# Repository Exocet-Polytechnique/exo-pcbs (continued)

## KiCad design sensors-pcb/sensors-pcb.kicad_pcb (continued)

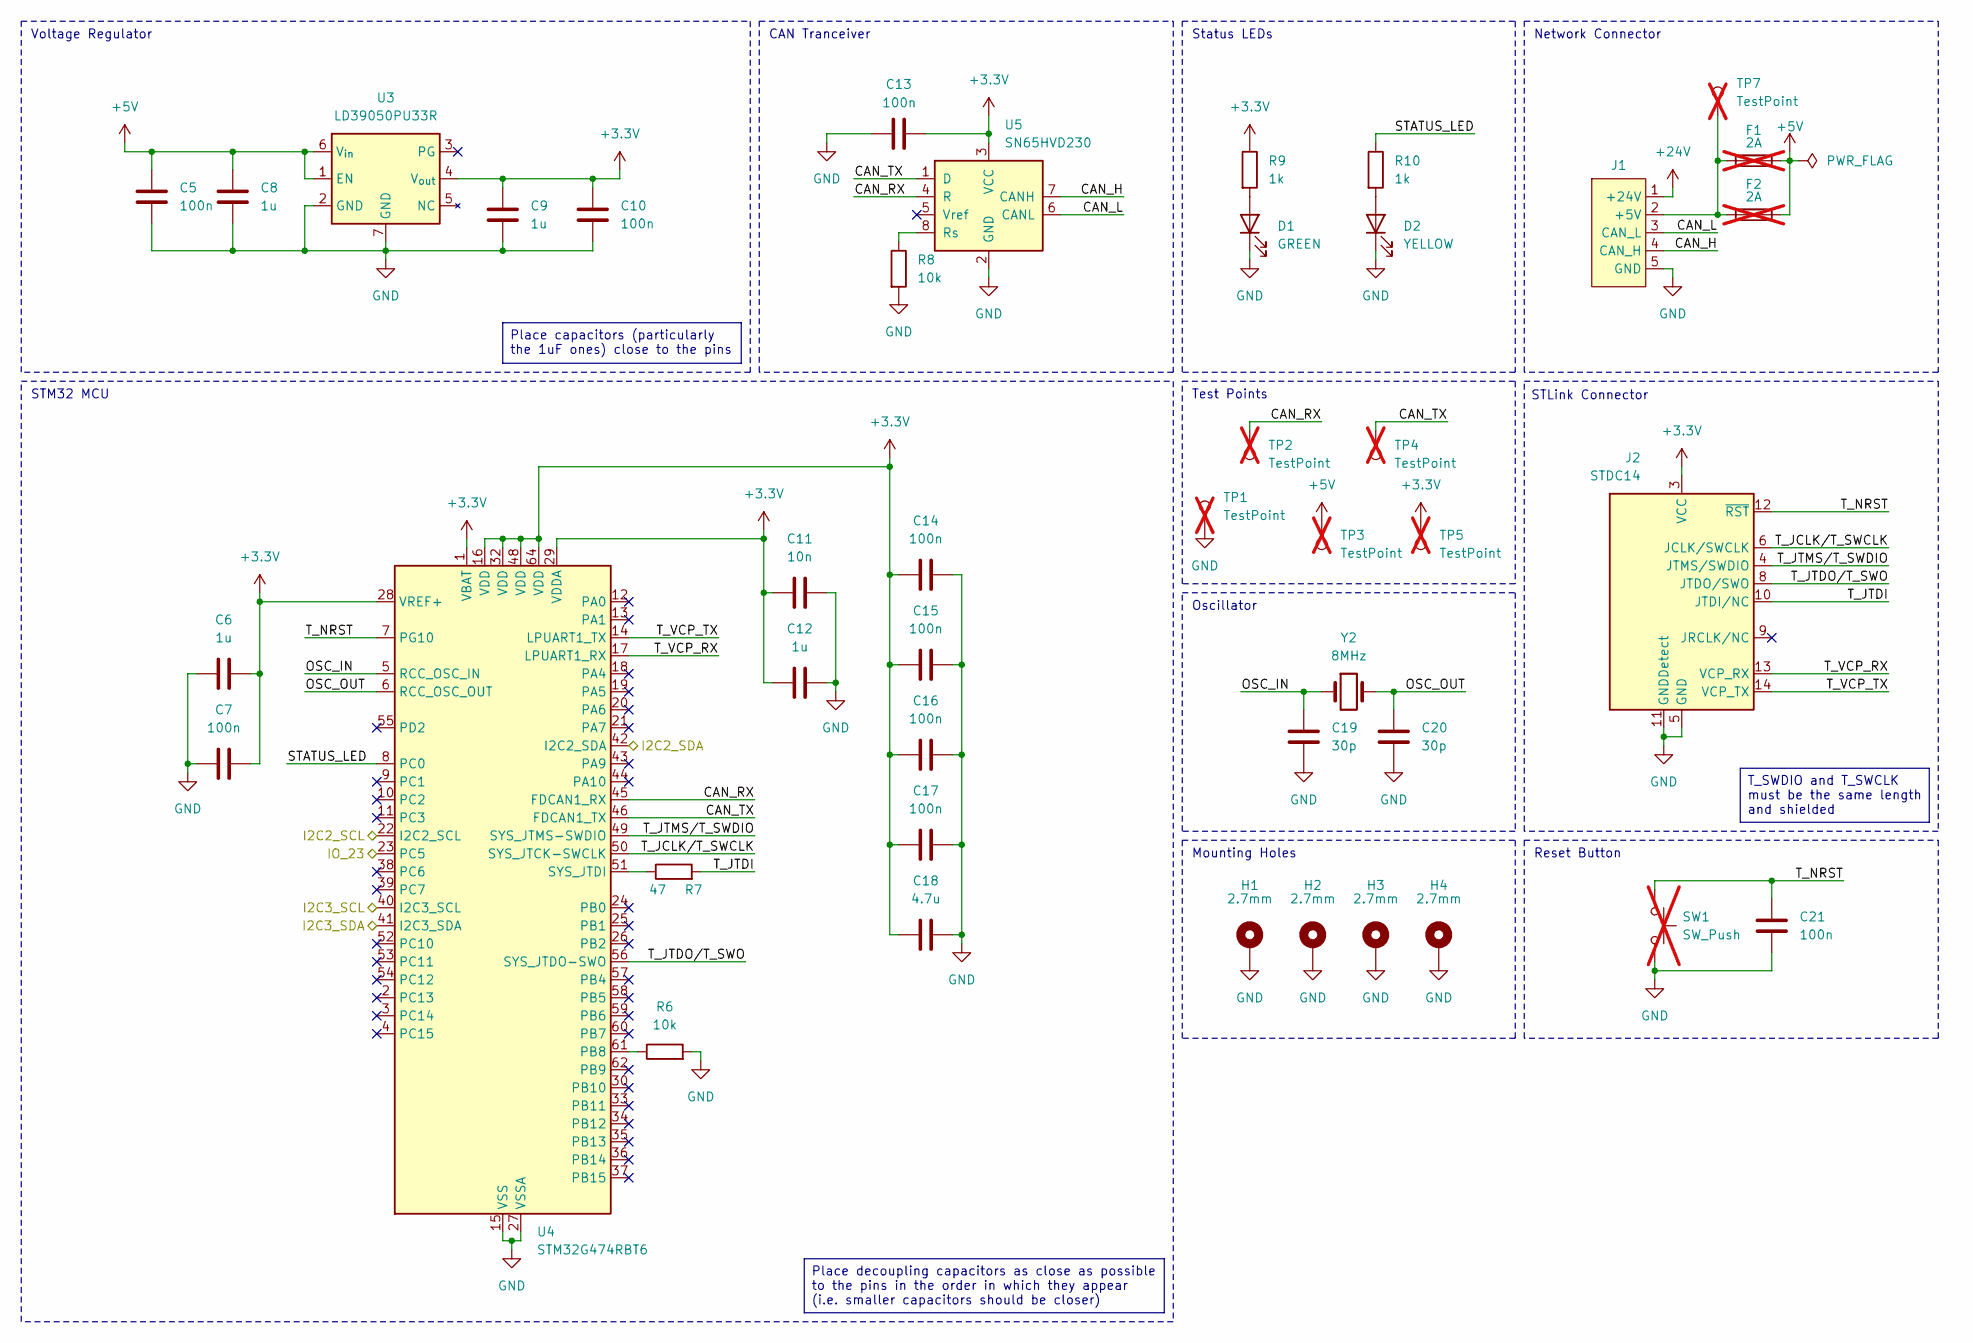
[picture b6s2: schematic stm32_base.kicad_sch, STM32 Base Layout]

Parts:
C5, C7, C10, C13, C14, C15, C16, C17, C21: 100n; C_0402_1005Metric; JLCPCB C1525
C6, C8, C9, C12: 1u; C_0402_1005Metric; JLCPCB C52923
C11: 10n; C_0402_1005Metric; JLCPCB C15195
C18: 4.7u; C_0402_1005Metric; JLCPCB C23733
C19, C20: 30p; C_0603_1608Metric; JLCPCB C1658
D1: GREEN; LED_0805_2012Metric_With_Annotations; JLCPCB C2297
D2: YELLOW; LED_0805_2012Metric_With_Annotations; JLCPCB C2296
F1: 2A; Fuse_Holder_Littelfuse_01530008; JLCPCB C206907; not fitted
F2: 2A; Fuseholder_Clip-5x20mm_Littelfuse_111_Lateral_P18.80x5.00mm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; not fitted
H1, H2, H3, H4: 2.7mm; MountingHole_2.7mm_Pad
J1: Network Connector; Molex_SPOX_5268-05A_1x05_P2.50mm_Horizontal; JLCPCB C185201
J2: STDC14; PinHeader_2x07_P1.27mm_Vertical_SMD; JLCPCB C7465995
R6, R8: 10k; R_0402_1005Metric; JLCPCB C25744
R7: 47; R_0603_1608Metric; JLCPCB C23182
R9, R10: 1k; R_0402_1005Metric; JLCPCB C11702
SW1: SW_Push; SW_PUSH_6mm; not fitted
TP1, TP2, TP3, TP4, TP5, TP7: TestPoint; TestPoint_Keystone_5005-5009_Compact; not fitted
U3: LD39050PU33R; DFN-6-1EP_3x3mm_P0.95mm_EP1.7x2.6mm; JLCPCB C132827
U4: STM32G474RBT6; LQFP-64_10x10mm_P0.5mm; JLCPCB C529413
U5: SN65HVD230; SOIC-8_3.9x4.9mm_P1.27mm; JLCPCB C12084
Y2: 8MHz; Crystal_SMD_HC49-SD; Part Name X49SM8MSD2SC; JLCPCB C12674

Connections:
+3.3V: C6.2, C7.2, C9.1, C10.1, C11.1, C12.1, C13.1, C14.1, C15.1, C16.1, C17.1, C18.1, J2.3 (VCC), R9.1, TP5.1, U3.4 (V_{out}), U4.1 (VBAT), U4.16 (VDD), U4.28 (VREF+), U4.29 (VDDA), U4.32 (VDD), U4.48 (VDD), U4.64 (VDD), U5.3 (VCC); also elsewhere on the board
+5V: C5.1, C8.1, F1.2, F2.2, TP3.1, U3.1 (EN), U3.6 (V_{in})
+24V: J1.1 (+24V)
/INT_IMU: U4.23 (PC5); also elsewhere on the board
/SCL_GPS: U4.40 (I2C3_SCL); also elsewhere on the board
/SCL_IMU: U4.22 (I2C2_SCL); also elsewhere on the board
/SDA_GPS: U4.41 (I2C3_SDA); also elsewhere on the board
/SDA_IMU: U4.42 (I2C2_SDA); also elsewhere on the board
/STM32 Base Layout/CAN_H: J1.4 (CAN_H), U5.7 (CANH)
/STM32 Base Layout/CAN_L: J1.3 (CAN_L), U5.6 (CANL)
/STM32 Base Layout/CAN_RX: TP2.1, U4.45 (FDCAN1_RX), U5.4 (R)
/STM32 Base Layout/CAN_TX: TP4.1, U4.46 (FDCAN1_TX), U5.1 (D)
/STM32 Base Layout/OSC_IN: C19.1, U4.5 (RCC_OSC_IN), Y2.1
/STM32 Base Layout/OSC_OUT: C20.1, U4.6 (RCC_OSC_OUT), Y2.2
/STM32 Base Layout/STATUS_LED: R10.1, U4.8 (PC0)
/STM32 Base Layout/T_JCLK/T_SWCLK: J2.6 (JCLK/SWCLK), U4.50 (SYS_JTCK-SWCLK)
/STM32 Base Layout/T_JTDI: J2.10 (JTDI/NC), R7.2
/STM32 Base Layout/T_JTDO/T_SWO: J2.8 (JTDO/SWO), U4.56 (SYS_JTDO-SWO)
/STM32 Base Layout/T_JTMS/T_SWDIO: J2.4 (JTMS/SWDIO), U4.49 (SYS_JTMS-SWDIO)
/STM32 Base Layout/T_NRST: C21.2, J2.12 (~RST), SW1.1, U4.7 (PG10)
/STM32 Base Layout/T_VCP_RX: J2.13 (VCP_RX), U4.17 (LPUART1_RX)
/STM32 Base Layout/T_VCP_TX: J2.14 (VCP_TX), U4.14 (LPUART1_TX)
GND: C5.2, C6.1, C7.1, C8.2, C9.2, C10.2, C11.2, C12.2, C13.2, C14.2, C15.2, C16.2, C17.2, C18.2, C19.2, C20.2, C21.1, D1.1 (K), D2.1 (K), H1.1, H2.1, H3.1, H4.1, J1.5 (GND), J2.5 (GND), J2.7 (GND), J2.11 (GNDDetect), R6.2, R8.2, SW1.2, TP1.1, U3.2 (GND), U3.7 (GND), U4.15 (VSS), U4.27 (VSSA), U4.31 (VSS), U4.47 (VSS), U4.63 (VSS), U5.2 (GND); also elsewhere on the board
unnamed: D1.2 (A), R9.2
unnamed: D2.2 (A), R10.2
unnamed: F1.1, F2.1, J1.2 (+5V), TP7.1
unnamed: R7.1, U4.51 (SYS_JTDI)
unnamed: R6.1, U4.61 (PB8)
unnamed: R8.1, U5.8 (Rs)

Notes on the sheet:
Oscillator
Reset Button
Mounting Holes
Voltage Regulator
CAN Tranceiver
Status LEDs
STLink Connector
Test Points
Network Connector
STM32 MCU
T_SWDIO and T_SWCLK must be the same length and shielded
Place capacitors (particularly the 1uF ones) close to the pins
Place decoupling capacitors as close as possible to the pins in the order in which they appear (i.e. smaller capacitors should be closer)

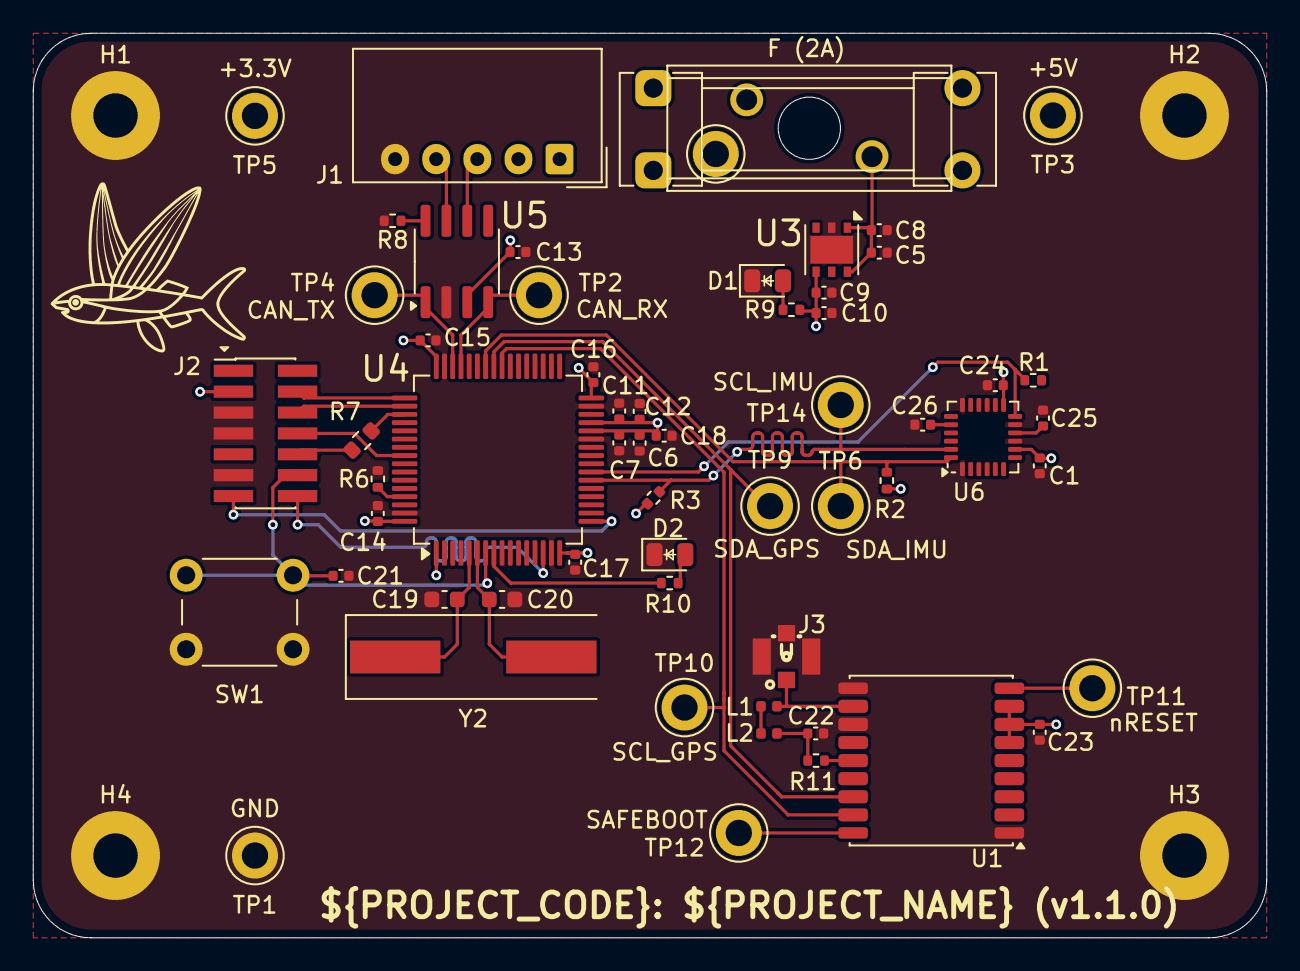
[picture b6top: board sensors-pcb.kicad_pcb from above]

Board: 2 copper layers, 75.0 x 55.0 mm, 64 parts (0 on the bottom side), 36 nets.

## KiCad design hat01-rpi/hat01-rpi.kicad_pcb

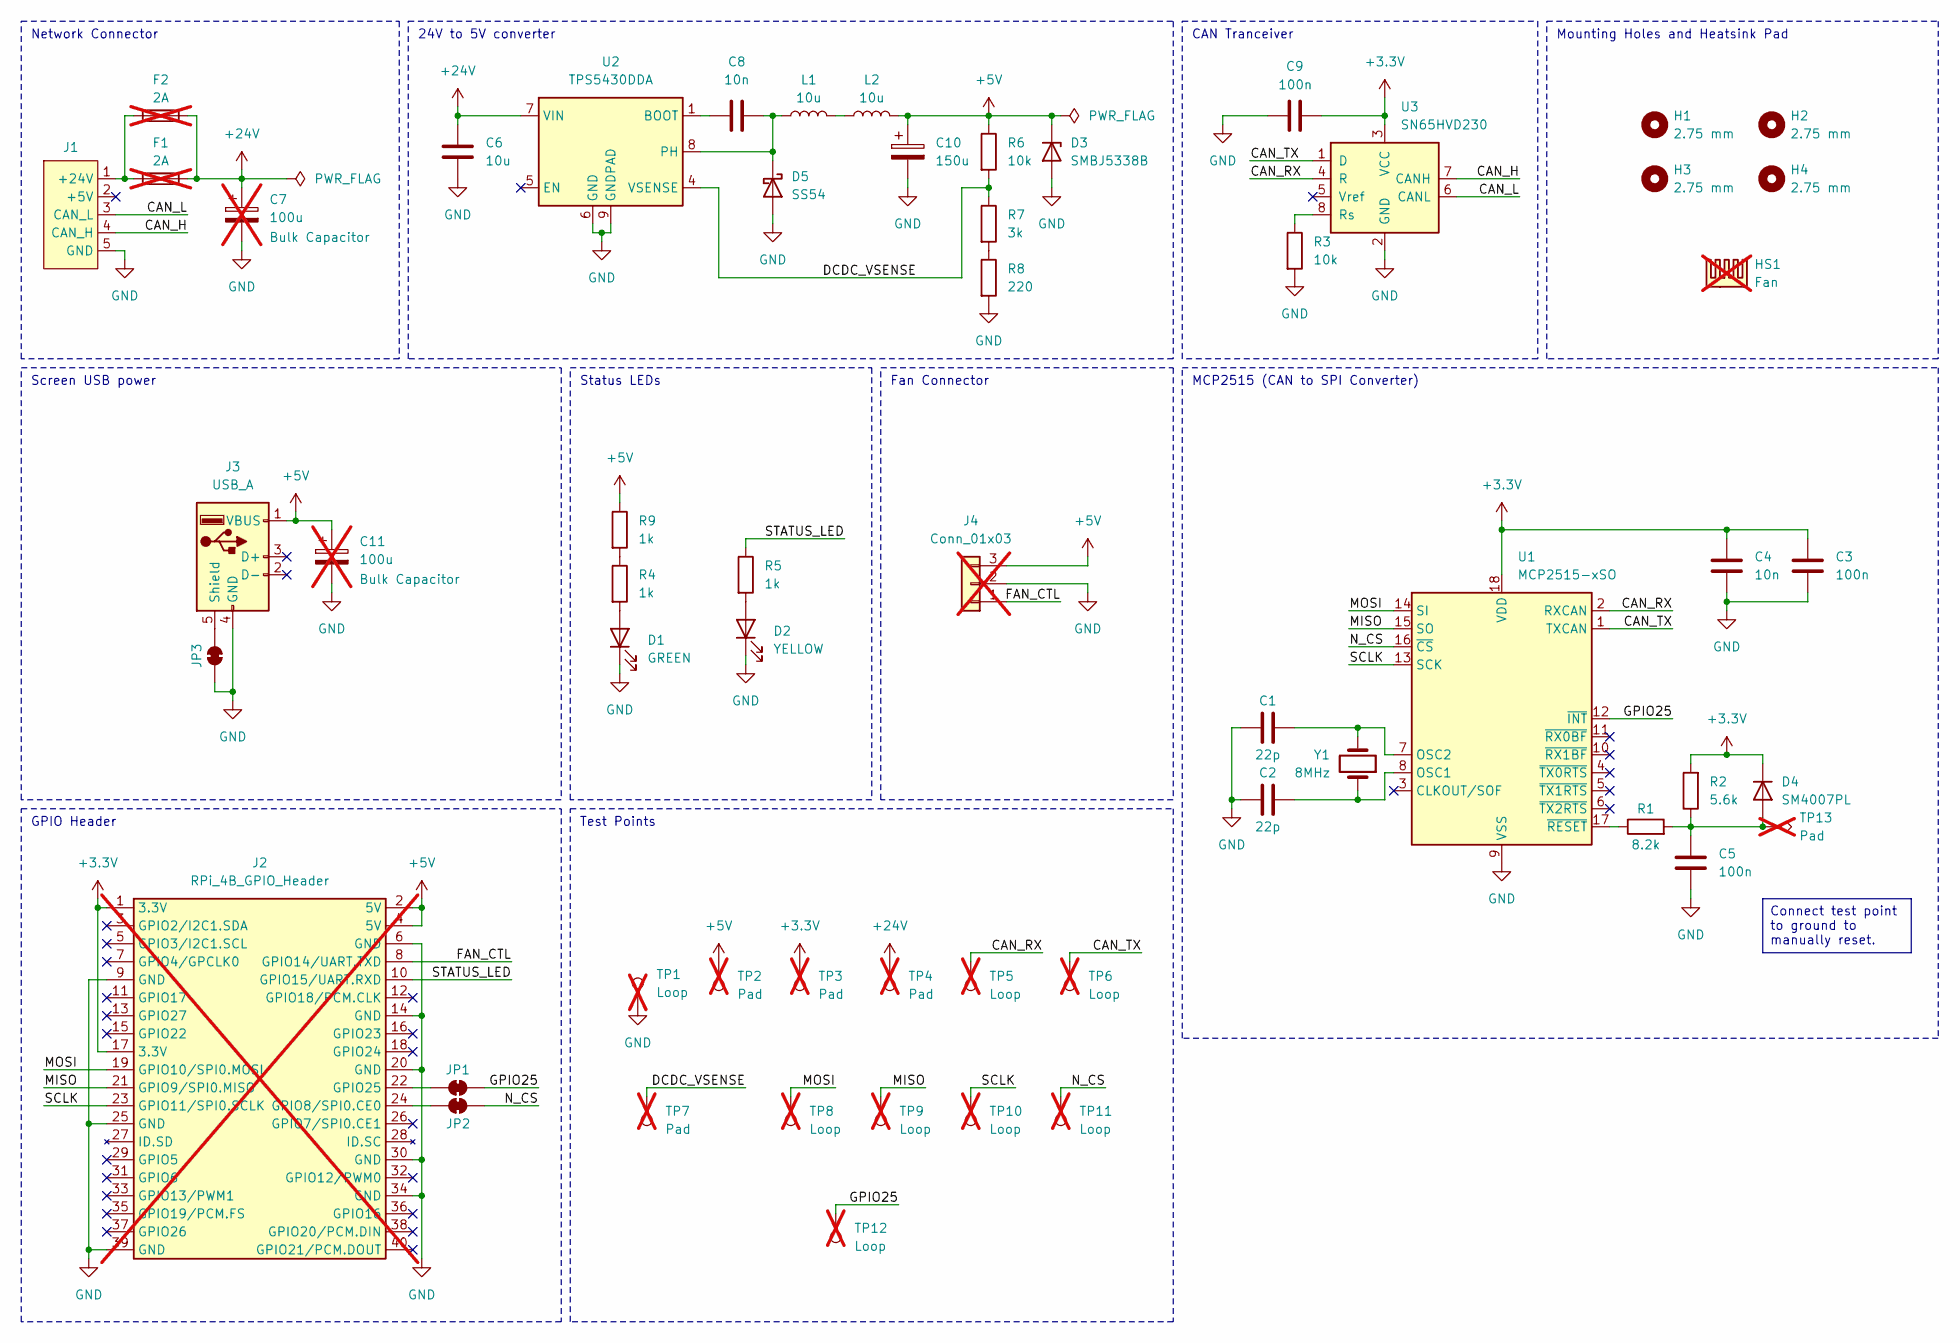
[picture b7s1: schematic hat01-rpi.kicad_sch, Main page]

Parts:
C1, C2: 22p; C_0402_1005Metric; JLCPCB C1555
C3, C5, C9: 100n; C_0402_1005Metric_Pad0.74x0.62mm_HandSolder; JLCPCB C1525
C4, C8: 10n; C_0402_1005Metric_Pad0.74x0.62mm_HandSolder; JLCPCB C15195
C6: 10u; C_1206_3216Metric_Pad1.33x1.80mm_HandSolder; JLCPCB C13585
C7, C11: 100u; CP_Radial_D8.0mm_P3.50mm; not fitted
C10: 150u; CP_Elec_6.3x7.7; JLCPCB C7471880
D1: GREEN; LED_0805_2012Metric_With_Annotations; JLCPCB C2297
D2: YELLOW; LED_0805_2012Metric_With_Annotations; JLCPCB C2296
D3: SMBJ5338B; D_SMB; JLCPCB C19077493
D4: SM4007PL; D_SOD-123F; JLCPCB C64898
D5: SS54; D_SMA_Handsoldering; JLCPCB C22452
F1: 2A; Fuse_Holder_Littelfuse_01530008; not fitted
F2: 2A; Fuseholder_Clip-5x20mm_Littelfuse_111_Lateral_P18.80x5.00mm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; not fitted
H1, H2, H3, H4: 2.75 mm; MountingHole_2.7mm_M2.5
HS1: Fan; RPi_Fan_Mount; not fitted
J1: Network Connector; Molex_SPOX_5268-05A_1x05_P2.50mm_Horizontal; JLCPCB C185201
J2: RPi_4B_GPIO_Header; PinSocket_2x20_P2.54mm_Vertical; not fitted
J3: USB_A; USB_A_Molex_67643_Horizontal; JLCPCB C2765194
J4: Conn_01x03; PinHeader_1x03_P2.54mm_Vertical; not fitted
JP1, JP2, JP3: SolderJumper_2_Bridged; SolderJumper-2_P1.3mm_Bridged_RoundedPad1.0x1.5mm
L1, L2: 10u; L_Changjiang_FXL0630; JLCPCB C167223
R1: 8.2k; R_0603_1608Metric_Pad0.98x0.95mm_HandSolder; JLCPCB C25981
R2: 5.6k; R_0603_1608Metric_Pad0.98x0.95mm_HandSolder; JLCPCB C23189
R3, R6: 10k; R_0603_1608Metric_Pad0.98x0.95mm_HandSolder; JLCPCB C25804
R4, R5, R9: 1k; R_0402_1005Metric_Pad0.72x0.64mm_HandSolder; JLCPCB C11702
R7: 3k; R_0603_1608Metric_Pad0.98x0.95mm_HandSolder; JLCPCB C4211
R8: 220; R_0402_1005Metric; JLCPCB C25091
TP1, TP5, TP6, TP8, TP9, TP10, TP11, TP12: Loop; TestPoint_Keystone_5005-5009_Compact; not fitted
TP2, TP3, TP4, TP7, TP13: Pad; TestPoint_Pad_D1.5mm; not fitted
U1: MCP2515-xSO; SOIC-18W_7.5x11.6mm_P1.27mm; JLCPCB C153782
U2: TPS5430DDA; TI_SO-PowerPAD-8_ThermalVias; JLCPCB C9864
U3: SN65HVD230; SOIC-8_3.9x4.9mm_P1.27mm; JLCPCB C12084
Y1: 8MHz; Crystal_SMD_HC49-SD; Part Name X49SM8MSD2SC; JLCPCB C12674

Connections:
+3.3V: C3.1, C4.1, C9.1, D4.1 (K), J2.1 (3.3V), J2.17 (3.3V), R2.2, TP3.1, U1.18 (VDD), U3.3 (VCC)
+5V: C10.1, C11.1, D3.1 (K), J2.2 (5V), J2.4 (5V), J3.1 (VBUS), J4.3, L2.2, R6.1, R9.1, TP2.1
+24V: C6.1, C7.1, F1.2, F2.2, TP4.1, U2.7 (VIN)
/CAN_H: J1.4 (CAN_H), U3.7 (CANH)
/CAN_L: J1.3 (CAN_L), U3.6 (CANL)
/CAN_RX: TP5.1, U1.2 (RXCAN), U3.4 (R)
/CAN_TX: TP6.1, U1.1 (TXCAN), U3.1 (D)
/DCDC_VSENSE: R6.2, R7.1, TP7.1, U2.4 (VSENSE)
/FAN_CTL: J2.8 (GPIO14/UART.TXD), J4.1
/GPIO25: JP1.2 (B), TP12.1, U1.12 (~INT)
/MISO: J2.21 (GPIO9/SPI0.MISO), TP9.1, U1.15 (SO)
/MOSI: J2.19 (GPIO10/SPI0.MOSI), TP8.1, U1.14 (SI)
/N_CS: JP2.2 (B), TP11.1, U1.16 (~CS)
/SCLK: J2.23 (GPIO11/SPI0.SCLK), TP10.1, U1.13 (SCK)
/STATUS_LED: J2.10 (GPIO15/UART.RXD), R5.1
GND: C1.1, C2.1, C3.2, C4.2, C5.2, C6.2, C7.2, C9.2, C10.2, C11.2, D1.1 (K), D2.1 (K), D3.2 (A), D5.2 (A), J1.5 (GND), J2.6 (GND), J2.9 (GND), J2.14 (GND), J2.20 (GND), J2.25 (GND), J2.30 (GND), J2.34 (GND), J2.39 (GND), J3.4 (GND), J4.2, JP3.1 (A), R3.2, R8.2, TP1.1, U1.9 (VSS), U2.6 (GND), U2.9 (GNDPAD), U3.2 (GND)
unnamed: D1.2 (A), R4.2
unnamed: D2.2 (A), R5.2
unnamed: C5.1, D4.2 (A), R1.2, R2.1, TP13.1
unnamed: C8.2, D5.1 (K), L1.1, U2.8 (PH)
unnamed: F1.1, F2.1, J1.1 (+24V)
unnamed: J2.24 (GPIO8/SPI0.CE0), JP2.1 (A)
unnamed: J2.22 (GPIO25), JP1.1 (A)
unnamed: J3.5 (Shield), JP3.2 (B)
unnamed: L1.2, L2.1
unnamed: R4.1, R9.2
unnamed: R7.2, R8.1
unnamed: C2.2, U1.8 (OSC1), Y1.1
unnamed: C1.2, U1.7 (OSC2), Y1.2
unnamed: R1.1, U1.17 (~RESET)
unnamed: C8.1, U2.1 (BOOT)
unnamed: R3.1, U3.8 (Rs)

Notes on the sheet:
24V to 5V converter
Fan Connector
GPIO Header
Screen USB power
CAN Tranceiver
Status LEDs
Mounting Holes and Heatsink Pad
Network Connector
MCP2515 (CAN to SPI Converter)
Test Points
Connect test point to ground to manually reset.

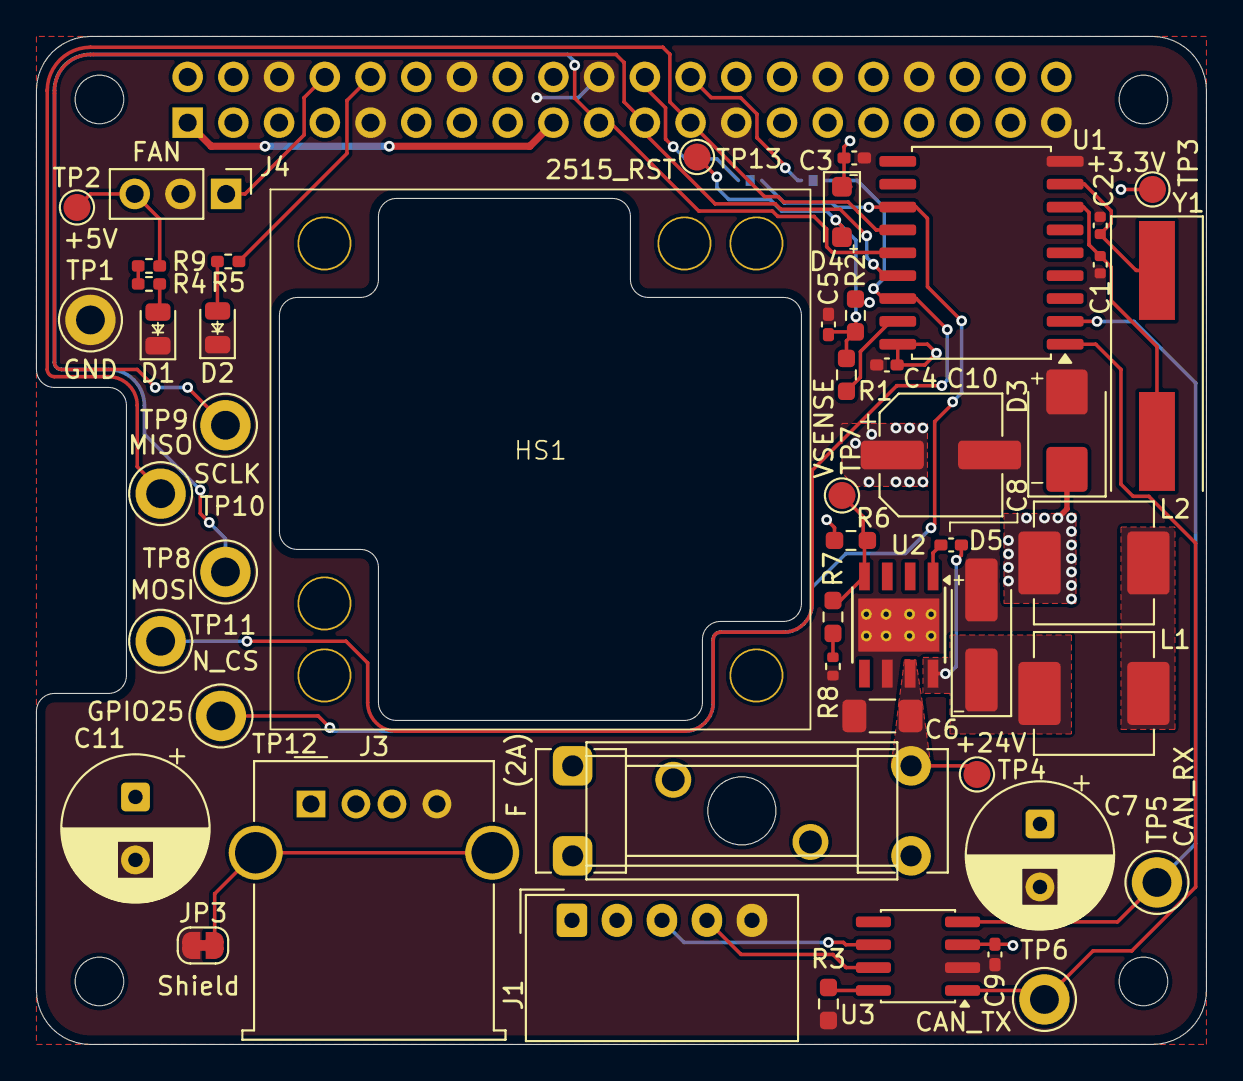
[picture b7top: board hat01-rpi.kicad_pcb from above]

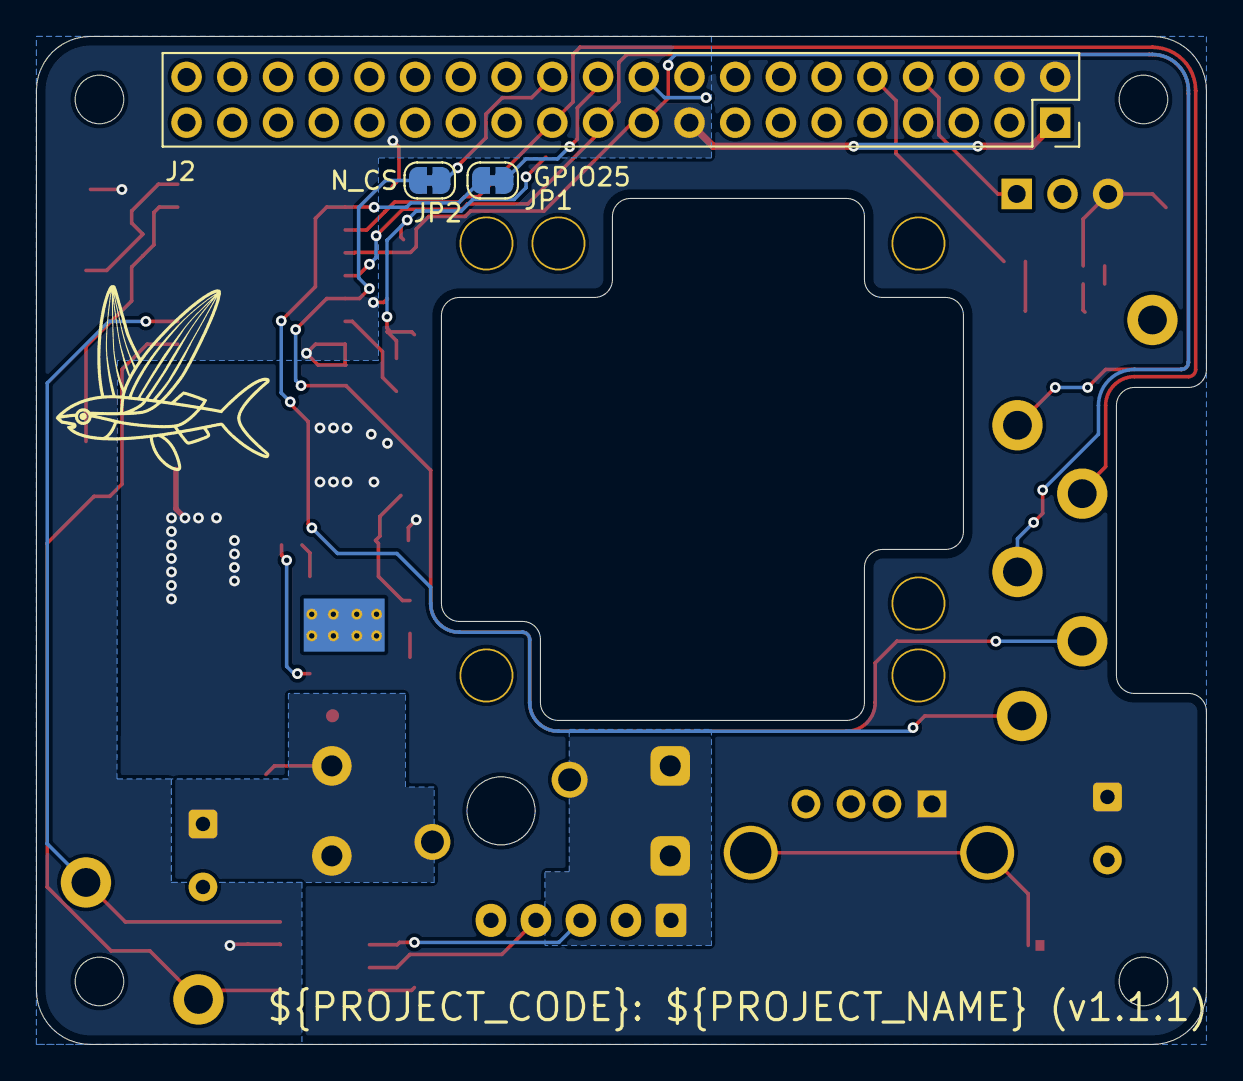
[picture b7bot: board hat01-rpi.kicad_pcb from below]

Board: 2 copper layers, 65.0 x 56.0 mm, 58 parts (3 on the bottom side), 32 nets.

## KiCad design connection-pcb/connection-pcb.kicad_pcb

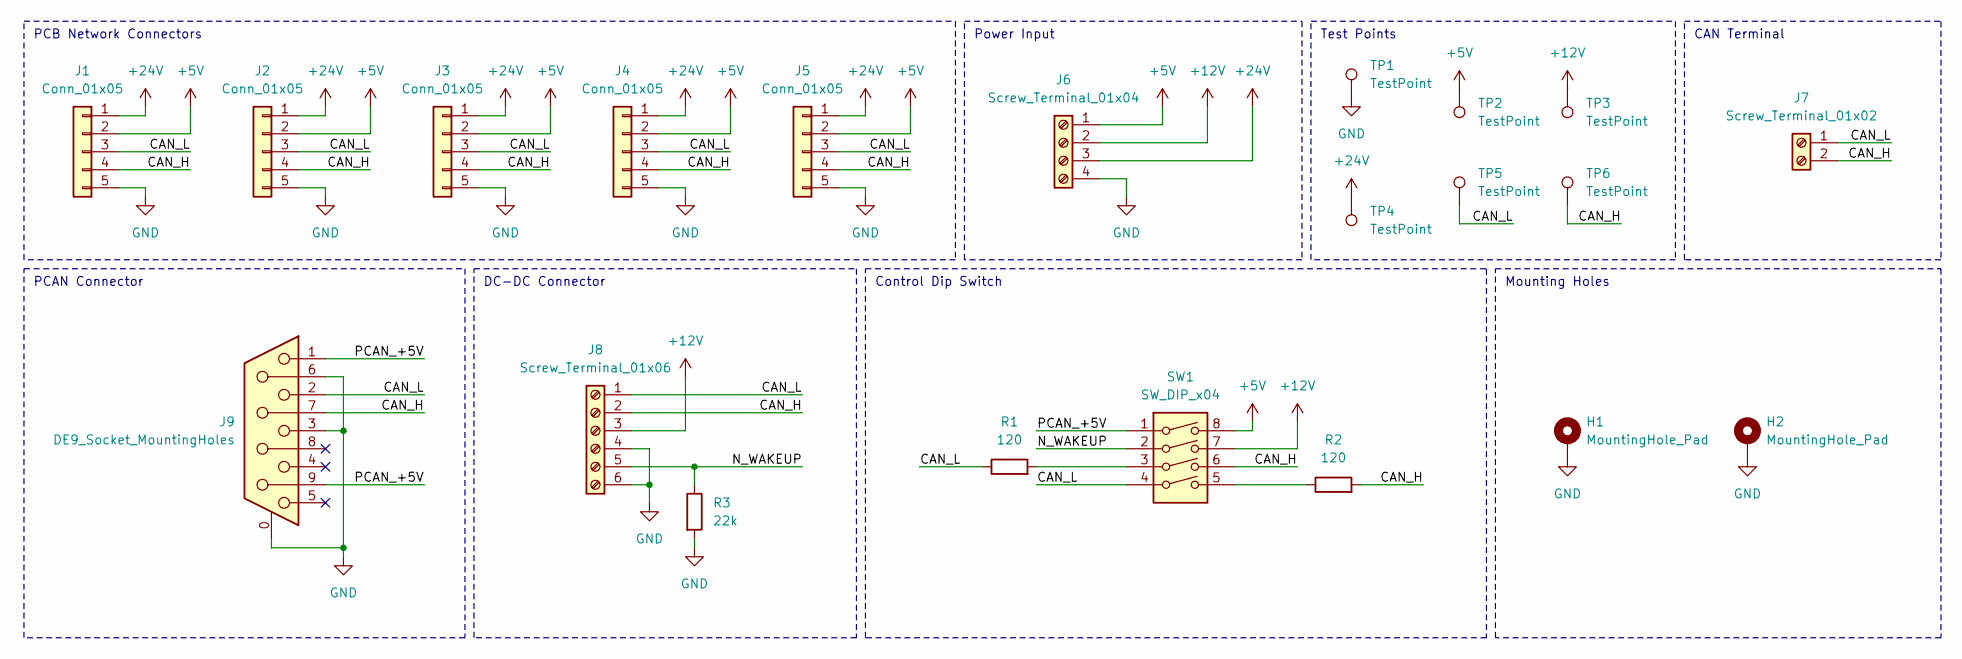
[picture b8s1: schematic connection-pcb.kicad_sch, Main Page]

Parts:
H1, H2: MountingHole_Pad; MountingHole_2.7mm_M2.5_ISO7380_Pad
J1, J2, J3, J4, J5: Conn_01x05; Molex_SPOX_5267-05A_1x05_P2.50mm_Vertical
J6: Screw_Terminal_01x04; Wurth_Term_Blk_4pos_Side_Entry_5mm
J7: Screw_Terminal_01x02; Wurth_Term_Blk_2pos_Side_Entry_5mm
J8: Screw_Terminal_01x06; Wurth_Term_Blk_6pos_Side_Entry_5mm
J9: DE9_Socket_MountingHoles; DSUB-9_Socket_Horizontal_P2.77x2.84mm_EdgePinOffset7.70mm_H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
R1, R2: 120; R_Axial_DIN0309_L9.0mm_D3.2mm_P12.70mm_Horizontal
R3: 22k; R_Axial_DIN0309_L9.0mm_D3.2mm_P12.70mm_Horizontal
SW1: SW_DIP_x04; SW_DIP_SPSTx04_Slide_6.7x11.72mm_W7.62mm_P2.54mm_LowProfile
TP1, TP2, TP3, TP4, TP5, TP6: TestPoint; TestPoint_Keystone_5005-5009_Compact

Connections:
+5V: J1.2, J2.2, J3.2, J4.2, J5.2, J6.1, SW1.8, TP2.1
+12V: J6.2, J8.3, SW1.7, TP3.1
+24V: J1.1, J2.1, J3.1, J4.1, J5.1, J6.3, TP4.1
/CAN_H: J1.4, J2.4, J3.4, J4.4, J5.4, J7.2, J8.2, J9.7, R2.2, SW1.6, TP6.1
/CAN_L: J1.3, J2.3, J3.3, J4.3, J5.3, J7.1, J8.1, J9.2, R1.1, SW1.4, TP5.1
/N_WAKEUP: J8.5, R3.1, SW1.2
/PCAN_+5V: J9.1, J9.9, SW1.1
GND: H1.1, H2.1, J1.5, J2.5, J3.5, J4.5, J5.5, J6.4, J8.4, J8.6, J9.0 (PAD), J9.3, J9.6, R3.2, TP1.1
unnamed: R1.2, SW1.3
unnamed: R2.1, SW1.5

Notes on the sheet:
Test Points
PCB Network Connectors
PCAN Connector
CAN Terminal
Control Dip Switch
DC-DC Connector
Power Input
Mounting Holes

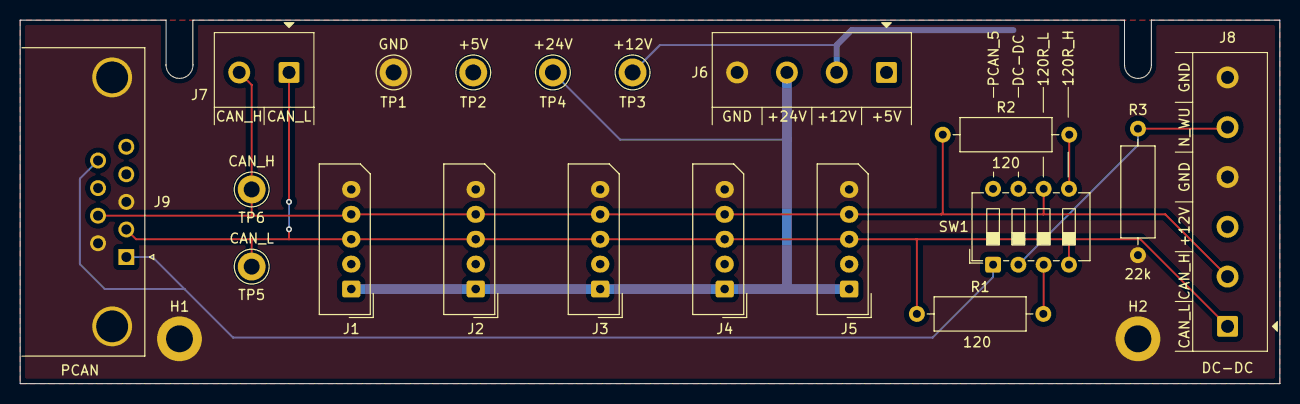
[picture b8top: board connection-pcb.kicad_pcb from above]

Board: 2 copper layers, 126.5 x 36.5 mm, 21 parts (0 on the bottom side), 10 nets.

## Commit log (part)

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2024-10-02 Change license to GPLv3
2024-11-20 TJA1050T
2024-11-27 Add oscillator
2024-11-27 Push-Button
2025-01-02 avancements sur l'alimentation du STM32
2025-01-04 Calculs pour les composantes
2025-01-05 changed CAN transceiver to SN65HVD23X
2025-01-07 network connector
2025-03-05 Schematics for the first version of the STM32 template
2025-03-09 Footprints and part numbers
2025-03-15 Initial placement and routing
2025-03-24 qqchose a été fait
2025-04-06 Add license to drawing sheet template
2025-04-06 Increase LED resistors
2025-04-06 Board routing
2025-04-06 Add components to schematic
2025-05-03 Connection PCB schematic
2025-05-03 Finish routing
2025-05-06 Fix unconnected trace
2025-05-29 Add Exocet logo
2025-06-06 Correct Exocet logo
2025-06-06 Remove Termination Resistor (CAN Network)
2025-06-06 Change B2B connector to STDC14 connector
2025-06-06 Connect BOOT0 to GND through 10k resistor
2025-06-06 template: move logo and change layer
    Logo is now in the top left, smaller and on the silkscreen layer
2025-06-09 template: add triangle to indicate first pin of STDC14 STLink connector
2025-06-12 template: change JLCPCB parts (capacitors & resistors)
2025-06-13 template: labels, traces, & parts placement corrections
2025-06-14 template: re-reference all components
    Had to re-add R1 and J2, but they were replaced where they were.
2025-06-14 h2-pcb: create project
    Created project from template v1.1.0
2025-06-14 misc: add 3d models submodule
    This is a private repo containing proprietary models and is therefore
    not available unless you have proper access to the repo.
2025-07-12 power-ctrl-pcb: initial project files
2025-07-16 telemetry-battery-pcb: add LTC2944
2025-07-22 telemetry-battery-pcb: complete LTC2944 circuitry
2025-07-23 telemetry-battery-pcb: add DC-DC Converter 24V->5V (TPS5430)
2025-08-01 telemetry-battery-pcb: corrections (battery gauge, EEPROM)
2025-08-11 h2-pcb: implement review comments in schematic
2025-08-13 telemetry-battery-pcb: add MOSFETs & change DC-DC Converter 24V->5V (TPSM86837)
2025-08-20 telemetry-battery-pcb: assign footprints (all except resistors and capacitors)
2025-08-23 Added footprints and jlc part numbers
2025-09-20 h2-pcb: implement review comments in footprint
2025-10-24 h2-pcb: Added fuse to +24V network connector pin in schematic
    Added a safety fuse of 5A to the +24V network connector pin
2025-11-02 Début du routage PCB Hydrogène : placement et début de routage.
2025-11-12 Ajusté symbole IMU et commencé schéma
2025-11-13 sensors-pcb: adjust IMU schematic and symbol
    hide no connect pins
    add connect I2C I/O to STM32 with pull-up resistors
    add external 42kHz clock from Exocet template
    pins 15 and 16 connected to GND through solder jumper
    because of conflicting datasheet info (2021 vs 2016). to be tested IRL
2025-11-14 sensors-pcb: add second solder junction
    in case connecting pins together is illegal
2025-11-24 telemetry-battery-pcb: create TPS1HTC30-Q1 symbol
2026-01-07 telemetry-battery-pcb: led circuit added
2026-01-16 misc: add .DS_Store to gitignore
2026-01-27 telemetry-battery-pcb: modify zener jlcpcb code
2026-01-28 telemetry-battery-pcb: updated JLC parts and footprints
2026-02-05 h2-pcb: add manometer, actuator and ds2428
2026-02-12 sensors-pcb: add footprints
2026-02-20 cooling: create project from stm32 template
2026-02-27 sensors-pcb: route IMU
2026-02-27 sensors-pcb: readded ground plane
    oups :P
2026-02-28 telemetry-battery-pcb: connections for TPS1HTC30-Q1
2026-03-01 telemetry_battery: modify footprint tps1htc30
2026-03-02 Update sur le routage, silkscreen, jlcpcb parts #
2026-03-02 telemetry-battery: Placements of parts
2026-03-03 telemetry-battery: modify footprint P-channel-Mosfet
2026-03-03 telemetry-battery : Routing of PCB
2026-03-04 Telemetry:Presque finis Routage
2026-03-07 h2-pcb: Fixed DRC errors + cleaned PCB
2026-03-08 Telemetry-battery: Routing of PCB changes: - add new diode model for tps1htc30-Q1 - Finish routing of tpshtc30-Q1 / DRC no error
2026-03-09 Telemetry-battery: Add thermal vias for Tps1htc30-Q1
2026-03-10 sensors-pcb: update resistor
    J'avais déjà associé la résistance 40k avec un code JLCPCB pour une 40.2k et elle semble être accessible donc voilà
2026-03-10 Telemetry-battery: Change Rlim value to 1,5k ohm based on new data
2026-03-12 h2-pcb: rename PA7 label to PB13
    The pin function for PB13 on the MCU was modified, but the hierarchical
    label wasn't updated. The one that used to be called "PA7" was renamed
    to "PB13" and connected to that pin.
    Also updated the routing to refelct these changes.
2026-03-15 telemetry-battery-pcb: move certains traces and vias
    Swapped nFAULT and LATCH signals to avoid vias on one of them. Removed
    90-degree corners on some traces. Move fuse for shorter traces.
2026-03-15 telemetry-battery-pcb: add info to silkscreen
    - Added net names to test points
    - Added battery polarity info
    - Added fuse current
    - Added PCB version
    - Added connector names and reset button label
2026-03-15 telemetry-battery-pcb: add GND_L plane
    For better thermal relief.
2026-03-15 telemetry-battery-pcb: remove layers from DC-DC symbol
2026-03-15 telemetry-battery-pcb: update JLCPCB component numbers
2026-03-15 h2-pcb: add test points to schematic
    - Updated PCB, but not routed yet
2026-03-15 h2-pcb: add fuse value to PCB silkscreen
2026-03-15 h2-pcb: make i2c traces parallel
2026-03-17 sensors-pcb: set TPs solder junctions as DNP
2026-03-17 sensors-pcb: connector SDA_GPS test point
2026-03-17 sensors-pcb: change 27nH to 10nH+15nH
2026-03-17 sensors-pcb: change antenna coax connector
2026-03-17 sensors-pcb: add IMU address text
2026-03-17 sensors-pcb: fix coax connector footprint
2026-03-17 sensors-pcb: ghost busted
    fixed fuse test point label
2026-03-19 telemetry-battery-pcb: change value of resistance - R27 - C29 - C27/C28 and others
2026-03-20 telemetry-battery-pcb: increase vias to 0.3mm of the tps1htc30-q1
2026-03-23 telemetry-battery-pcb: Review of pcb components and values
2026-03-24 h2-pcb: replace ds2484 symbol
    The symbol is now the one from the official KiCad library. PCB was also
    updated and any remaining DRC errors were fixed.
2026-03-28 power-pcb: update project metadata
    Also added project code, name and version to silkscreen in the board
    layout.
2026-03-29 h2-pcb: add plane for left actuator connectors
2026-04-02 h2-pcb: Add 24V zone for connectors, change footprint for temp sensors + connect
    Made 24V zone for right actuators connectors, network connector and 24V fuse holder.
    Changed the temperature sensor connectors to JST_PH_S3B-PH-k_1x03_P2.00mm_Horizontal and placed them on the left side of pcb.
    Followed with connecting the temperature sensors on the pcb.
    TODO : fix 5 errors in DRC.
2026-04-04 sensors-pcb: finalize v1.1.0 metadata
    Added Guillaume as reviewer and updated the date to the last
    modification.
    Also added missing JLCPCB part number to the MPU-6050 symbol.
2026-04-05 h2-pcb: Fix DRC errors
    Rotated the right actuator connectors and moved the zones to include the 3.3V zone with the rest of its zone. Added a zone for the Net J1 24V.
2026-04-05 telemetry-battery-pcb: Changes on footprints Rlim and R30
2026-04-06 h2-pcb: change value of LED resistors
2026-04-06 h2-pcb: add fuse holder 01110501Z
2026-04-06 h2-pcb: flip actuator connectors 3 & 4 to front layer
2026-04-07 hat01-rpi: minors improvements to board part data
    Some components needed to be marked as DNP/exclude from BOM. Finished
    rounding some traces around corners. Added some information on the
    Silkscreen. This commit was not directly used for the order (this is
    v1.1.1, not v1.1.0), but some modifications were added to the previous
    version before the order.
2026-04-08 h2-pcb: add fuse holder 01110501Z for 5A
2026-04-08 sensors-pcb: add some 3d-models
2026-04-08 hat01-rpi: add some 3d models
2026-04-11 telemetry-battery-pcb: add combined fuseholder footprint
    This gets rid of all remaining DRC warnings and makes the schematic a
    little clearer.
2026-04-11 telemetry-battery-pcb: change SNS to 5V-tolerant pin
2026-04-12 telemetry-battery-pcb: fix ERC errors/warnings
2026-04-12 telemetry-battery-pcb: review 24V network switch
    Also reverted to the preivous chip we wanted to use that was no longer
    available, but is now.
2026-04-12 telemetry-battery-pcb: change capacitor part numbers
    Some capacitors did not support the required voltage. Also, some had the
    incorrect footprint and were updated.
    Also added some test points.
2026-04-15 telemetry-battery-pcb: update LTC2944 JLCPCB number
2026-05-09 board relais : version 1
2026-05-31 version 3
2026-06-01 relay-board: rename project and update to KiCad 10
2026-06-01 relay-board: split schematic into pages
2026-06-01 relay-board: update footprint and symbol libs
2026-06-01 relay-board: change 25-pin connector symbol
    Also fixed all ERC warnings and renamed nets to match those of the
    power-pcb project.
2026-06-03 power-pcb: reduce optocoupler diode and add fuse
    Also added a connector to select the source of for the 24-V net
    going into the contactor coils.
    Reducing the value of the resistor will ensure there is enough current
    to close the 5V relay.
2026-06-05 relay-board: finish routing pcb
2026-06-13 power-pcb: finish schematic pages 1 to 7
    - overview
    - non-isolated interfaces + power
    - stm32 microcontroller
    - relay board connection
    - battery sensors
    - 48v i-v sensing (x2)
2026-06-14 power-pcb: finish schematic layout
    All parts are placed and connected, ERC passes (except for two
    exclusions with comment).
2026-06-15 power-pcb: configure JLCPCB variant
    Set parts not assembled by JLCPCB as DNP.
2026-06-18 relay-board: remove 3.3V input
    Reduces risk of shorts and was not necessary to begin with. Now inputs
    are active high, which is also less prone to mistakes on the programming
    side.
2026-06-20 relay-board: finish pcb layout
2026-06-20 power-pcb: work on part placement and JLCPCB DNP
    Some of the components that were recentlt added had not been marked as
    DNP for JLCPCB yet, this is now done.
2026-06-21 power-pcb: finish placement and started routing
    Started routing power traces only and didn't place test points yet.
2026-06-21 power-pcb: route battery-sensing traces
2026-06-25 hat01-rpi: Mark D3 and DNP
    This diode's zener voltage was too low and would conduct in normal
    operation. It was removed since it would heat up and is not particularly
    useful.
2026-06-25 telemetry-battery-pcb: change regulator part
    PMB: increased the max current of the regulator after it stopped
    working.
2026-06-27 power-breadboard: create project and remove unused
    Copied the schematic from the power-pcb project at the previous commit
    and removed many components that will not be present on the breadboard.
2026-06-29 power-breadboard: rename stm32 sheet to nucleo
    Also removed unused sheet pins on main page.
2026-06-29 power-breadboard: rename relay-board page
    There are now multiple relay boards.
    Also cleaned up some sheet pins on the main page.
2026-06-29 power-breadboard: finish relay board connections
    Updateed to use separarate relay boards. Also updated hierarchical
    labels and sheet pins.
2026-06-29 power-breadboard: finish battery temp. sensing
